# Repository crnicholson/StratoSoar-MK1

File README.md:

<picture>
 <source media="(prefers-color-scheme: dark)" srcset="https://github.com/charlienicholson3/StratoSoar/blob/main/schematic.png?raw=true">
 <source media="(prefers-color-scheme: light)" srcset="https://github.com/charlienicholson3/StratoSoar/blob/main/schematic.png?raw=true">
 
</picture>

# UPDATE: This project is on its second year in a different repo as StratoSoar MK2. Link here: https://github.com/charlienicholsonr/StratoSoar-MK2.

### NOTE: This PCB is wrong. We had to add a wire to the board. I suggest designing your own PCB.

# StratoSoar MK1
My repo for the StratoSoar project. The LightAPRS code is just a variation of the original code. This system is made to recover unmanned high-altitude gliders, launched from weather balloons. It also has sensors that write to EEPROM, and the power for that system is controlled by the main MCU, which is the LightAPRS. For those who do not know, APRS is a form of HAM radio. You need to be a HAM radio operator to do it. For those who do not know, LightAPRS W-2 is a lightweight APRS transmitter: github.com/lightaprs/LightAPRS-W-2.0. The PCB takes anything from 20 to 6 volts as input and turns off the sensor and the camera after a certain altitude. It can also control the recording of the video. The schematic shows everything. The PCB breaks into three parts: top, middle, and bottom layers that connect through header pins.

# Acknowledgements
Thanks to Harish KC1SIO for the idea and initial work. Thanks to the NEWBS team for fostering the idea and having the high altitude project. Special thanks to Max W0MXX and Seth KC1PZY for funding and help during this project. Thanks to Bob K5TEC at NeSciTech for supplying a workspace and collaboration area. 

# Nerd info
We used a RunCam DVR with a 2N2222 transistor to close the circuit where the button is mounted. This took lots of development and didn't always go right. It highly depends on the voltage of the MCU and the amount of current your MCU can sink into the base pin of the transistor. Because of this, we had to not use the Serial Wombat and to solder a wire onto the LightAPRS. The SerialWombat can still be used to power the MOSFET, though it should be noted that the voltage goes through a series of transistor amplifiers to have enough voltage to turn on the FET. The camera on the DVR was a RunCam Atom.

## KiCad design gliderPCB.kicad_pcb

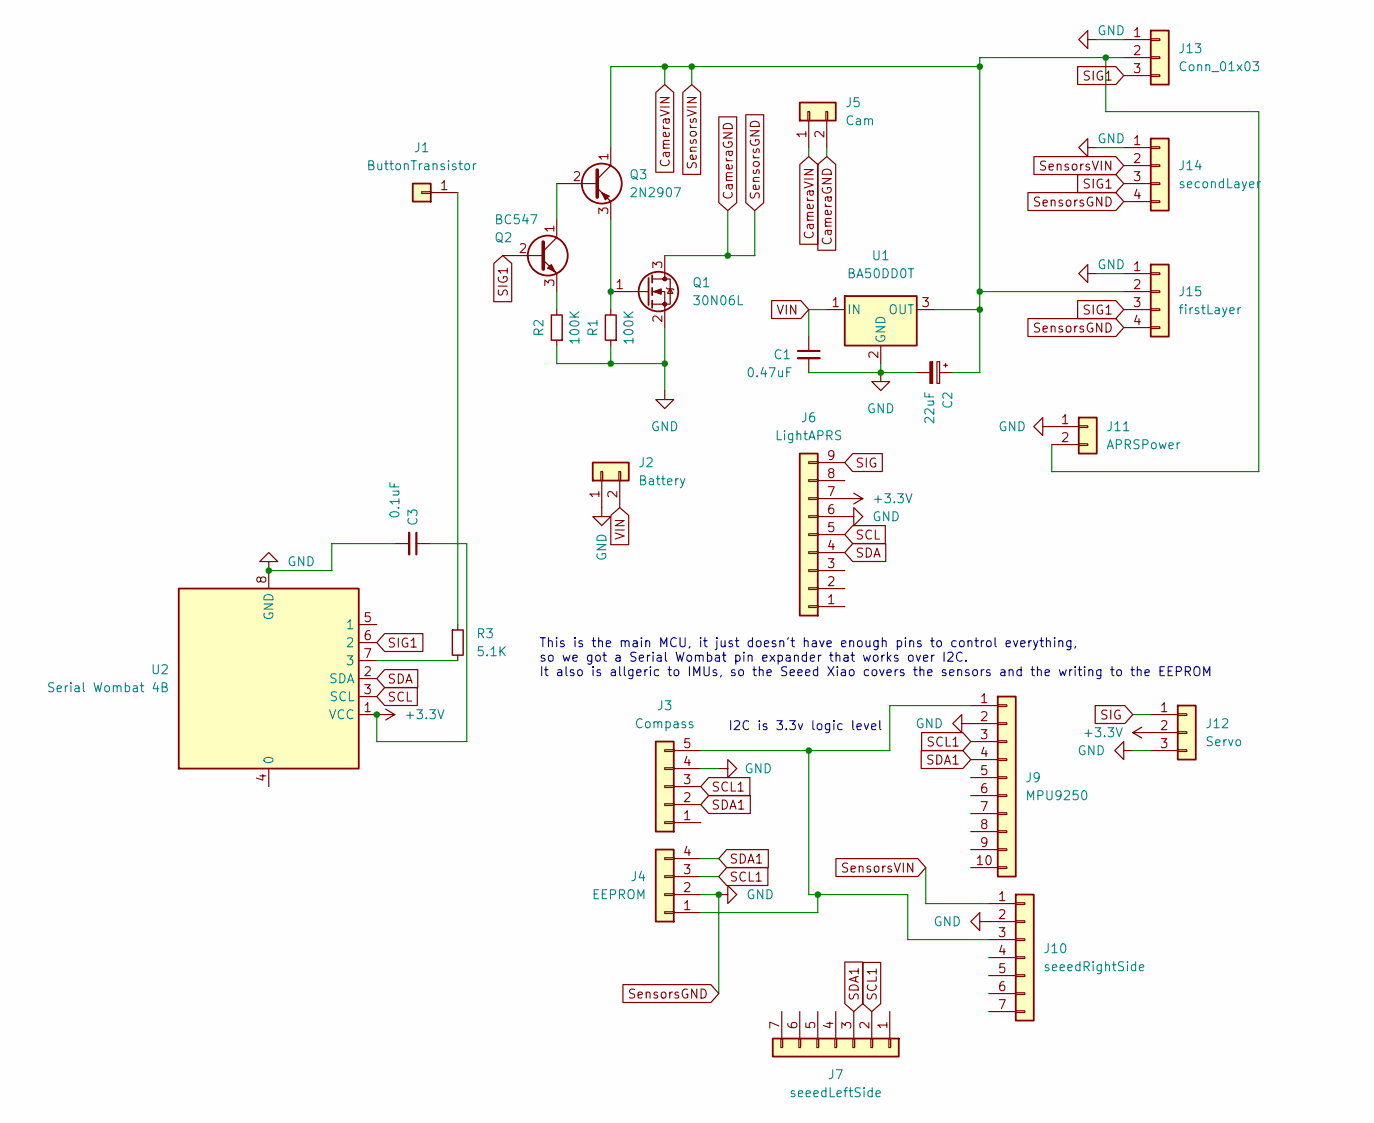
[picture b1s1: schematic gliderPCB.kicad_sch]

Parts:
C1: 0.47uF; C_Disc_D4.3mm_W1.9mm_P5.00mm
C2: 22uF; CP_Radial_D5.0mm_P2.50mm
C3: 0.1uF; C_Disc_D4.3mm_W1.9mm_P5.00mm
J1: ButtonTransistor; PinHeader_1x01_P2.54mm_Vertical
J2: Battery; PinHeader_1x02_P2.54mm_Vertical
J3: Compass; PinHeader_1x05_P2.54mm_Vertical
J4: EEPROM; PinHeader_1x04_P2.54mm_Vertical
J5: Cam; PinHeader_1x02_P2.54mm_Vertical
J6: LightAPRS; PinHeader_1x09_P2.54mm_Vertical
J7: seeedLeftSide; PinHeader_1x07_P2.54mm_Vertical
J9: MPU9250; PinHeader_1x10_P2.54mm_Vertical
J10: seeedRightSide; PinHeader_1x07_P2.54mm_Vertical
J11: APRSPower; PinHeader_1x02_P2.54mm_Vertical
J12: Servo; PinHeader_1x03_P2.54mm_Vertical
J13: Conn_01x03; PinHeader_1x03_P2.54mm_Vertical
J14: secondLayer; PinHeader_1x04_P2.54mm_Vertical
J15: firstLayer; PinHeader_1x04_P2.54mm_Vertical
Q1: 30N06L; TO-220-3_Vertical
Q2: BC547; TO-92L_Inline
Q3: 2N2907; TO-92L_Inline
R1, R2: 100K; R_Axial_DIN0207_L6.3mm_D2.5mm_P10.16mm_Horizontal
R3: 5.1K; R_Axial_DIN0207_L6.3mm_D2.5mm_P10.16mm_Horizontal
U1: BA50DD0T; TO-220F-3_Vertical
U2: Serial Wombat 4B; DIP-8_W7.62mm

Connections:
+3.3V: C3.1, J6.7, J12.2, U2.1 (VCC)
CameraGND: C1.2, C2.2, C3.2, J2.1, J3.4, J4.2, J5.2, J6.6, J9.2, J10.2, J11.1, J12.3, J13.1, J14.1, J14.4, J15.1, J15.4, Q1.2 (S), Q1.3 (D), R1.1, R2.1, U1.2 (GND), U2.8 (GND)
CameraVIN: C2.1, J5.1, J10.1, J11.2, J13.2, J14.2, J15.2, Q3.1 (C), U1.3 (OUT)
unnamed: J1.1, R3.1
unnamed: J3.5, J4.1, J9.1, J10.3
unnamed: Q1.1 (G), Q3.3 (E), R1.2
unnamed: Q2.1 (C), Q3.2 (B)
unnamed: Q2.3 (E), R2.2
unnamed: R3.2, U2.7 (3)
SCL: J6.5, U2.3 (SCL)
SCL1: J3.3, J4.3, J7.2, J9.3
SDA: J6.4, U2.2 (SDA)
SDA1: J3.2, J4.4, J7.3, J9.4
SIG: J6.9, J12.1
SIG1: J13.3, J14.3, J15.3, Q2.2 (B), U2.6 (2)
VIN: C1.1, J2.2, U1.1 (IN)

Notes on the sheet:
I2C is 3.3v logic level
This is the main MCU, it just doesn't have enough pins to control everything, so we got a Serial Wombat pin expander that works over I2C. It also is allgeric to IMUs, so the Seeed Xiao covers the sensors and the writing to the EEPROM

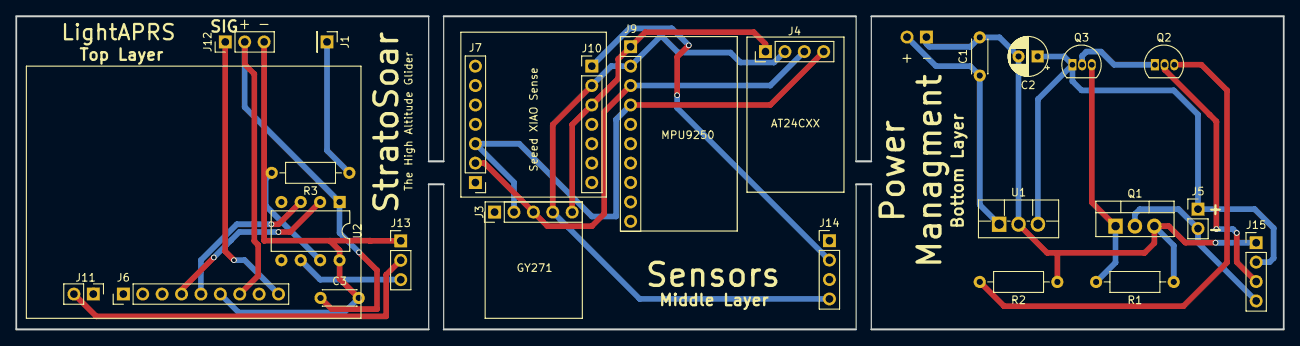
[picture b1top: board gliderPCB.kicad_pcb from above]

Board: 2 copper layers, 166.0 x 41.0 mm, 25 parts (1 on the bottom side), 16 nets.

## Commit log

2023-05-17 StratoSoar gerber files
2023-05-17 Schematic
2023-05-17 LightAPRS W-2 code
2023-05-17 Code for sensors
    Upload this to the Seeed Studio XIAO BLE Sense
